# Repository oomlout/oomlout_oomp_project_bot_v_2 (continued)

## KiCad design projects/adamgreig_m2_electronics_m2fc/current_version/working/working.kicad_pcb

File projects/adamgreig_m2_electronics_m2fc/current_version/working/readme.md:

# m2_electronics
 
## summary 
* id: adamgreig_m2_electronics_m2fc
* user: adamgreig
* name: m2_electronics
* board: m2fc
* repo: https://github.com/adamgreig/m2-electronics
* src_file_repo_kicad_pcb: m2fc/pcb/m2fc.kicad_pcb
* src_file_repo_kicad_pcb_link: https://github.com/adamgreig/m2-electronics/tree/master/m2fc/pcb/m2fc.kicad_pcb

* src_file_repo_sch: 
* src_file_repo_sch_link: https://github.com/adamgreig/m2-electronics/tree/master/
* full details link: https://github.com/oomlout/oomlout_oomp_project_bot_v_2/tree/main/projects/adamgreig_m2_electronics_m2fc/current_version/working  

## schematic  
  
[schematic (pdf)](working_schematic.pdf) 

## pcb  

[board (pdf)](working.pdf)  

## working_bom
| Id | Designator | Footprint | Quantity | Designation | Supplier and ref |  | None | 
| --- | --- | --- | --- | --- | --- | --- | --- | 
| 1 | C101,C104,C106,C120,C124,C126,C119 | C0603 | 7 | 2Âµ2 |  |  | [''] | 
| 2 | C102,C103,C108,C110,C111,C112,C113,C115,C116,C209,C210,C211,C212,C222,C223,C224,C225,C235,C236,C237,C238,C301,C302,C307,C308,C310,C403,C404,C405,C406,C407,C408,C501,C502,C503,C601,C604,C612,C615,C623,C626,C114,C305,C304,C122 | C0603 | 45 | 100n |  |  | [''] | 
| 3 | C105,C125 | C0603 | 2 | 1n |  |  | [''] | 
| 4 | C107,C109,C204,C205,C206,C213,C217,C219,C226,C230,C231,C232,C239,C303,C309,C401,C402,C602,C605,C616,C624,C627,C218,C613,C306 | C0603 | 25 | 10Âµ |  |  | [''] | 
| 5 | C117,C608,C619,C630 | C0603 | 4 | 1Âµ |  |  | [''] | 
| 6 | C118,C201,C214,C227,C311,C609,C610,C620,C621,C631,C632 | C0603 | 11 | 10n |  |  | [''] | 
| 7 | C121,C123 | C0603 | 2 | 15p |  |  | [''] | 
| 8 | C202,C203,C215,C216,C228,C229 | C0603 | 6 | 82n |  |  | [''] | 
| 9 | C207,C208,C220,C221,C233,C234 | C0603 | 6 | 8.2n |  |  | [''] | 
| 10 | C312 | C0603 | 1 | 220n |  |  | [''] | 
| 11 | C313 | C0603 | 1 | 470n |  |  | [''] | 
| 12 | C314 | C0603 | 1 | 4Âµ7 |  |  | [''] | 
| 13 | C603,C606,C607,C611,C614,C617,C618,C622,C625,C628,C629,C633 | C1206 | 12 | 100n |  |  | [''] | 
| 14 | D101,D102,D201,D202,D203,D204,D205,D206,D406,D407,D504,D506,D603,D604,D605,D606,D601,D602,D502 | R0402 | 19 | CGA0402MLC-12G |  |  | [''] | 
| 15 | D402,D403,D404,D405 | LED0603 | 4 | YELLOW |  |  | [''] | 
| 16 | D501,D503,D505 | SOD323 | 3 | DIODESCH |  |  | [''] | 
| 17 | IC101,IC103 | MSOP8 | 2 | ADP3335 |  |  | [''] | 
| 18 | IC102 | LQFP100 | 1 | STM32F405VGT |  |  | [''] | 
| 19 | IC201,IC204,IC207 | MSOP8 | 3 | AD8226 |  |  | [''] | 
| 20 | IC202,IC208,IC602,IC604,IC606,IC205 | MSOP8 | 6 | AD8656 |  |  | [''] | 
| 21 | IC203,IC206,IC209 | SC-70-5 | 3 | AD8541 |  |  | [''] | 
| 22 | IC301 | ADXL3x5 | 1 | ADXL375 |  |  | [''] | 
| 23 | IC303 | MS5611-01BA | 1 | MS5611-01BA03 |  |  | [''] | 
| 24 | IC304 | HMC5883L | 1 | HMC5883L |  |  | [''] | 
| 25 | IC305 | L3G4200D | 1 | L3G4200D |  |  | [''] | 
| 26 | IC401 | SOIC16 | 1 | ADuM5201 |  |  | [''] | 
| 27 | IC402 | SOIC8 | 1 | ADuM1201 |  |  | [''] | 
| 28 | IC601,IC603,IC605 | MSOP8 | 3 | AD8495 |  |  | [''] | 
| 29 | P101,P402,P503,P601,P602,P603,P502,P501,P102,P103 | S02B-PASK-2 | 10 | CONN_2 |  |  | [''] | 
| 30 | P104 | FTSH-105-01-F-D-K | 1 | SWD |  |  | [''] | 
| 31 | P201,P202,P203,P403,P401 | S04B-PASK-2 | 5 | CONN_4 |  |  | [''] | 
| 32 | R101,R301,R304,R306,R307,R308,R501,R504,R506,R507,R508,R511,R513,R514,R515,R518,R520,R521,R303,R305,R302 | R0603 | 21 | 10k |  |  | [''] | 
| 33 | R102,R201,R209,R217,R601,R606,R608,R613,R615,R620 | R0603 | 10 | 1k |  |  | [''] | 
| 34 | R105,R106,R107,R104,R103 | R0603 | 5 | 47k |  |  | [''] | 
| 35 | R108,R401,R402,R403,R404,R405,R406,R407,R502,R503,R509,R510,R516,R517,R408 | R0603 | 15 | 100 |  |  | [''] | 
| 36 | R202,R208,R210,R218,R216,R224 | R0603 | 6 | 10k 0.05% |  |  | [''] | 
| 37 | R203,R211,R219 | R0603 | 3 | 330 |  |  | [''] | 
| 38 | R204,R212,R220 | R0603 | 3 | 1.69k |  |  | [''] | 
| 39 | R205,R213,R221 | R0603 | 3 | 6.04k |  |  | [''] | 
| 40 | R206,R214,R222 | R0603 | 3 | 562 |  |  | [''] | 
| 41 | R207,R215,R223 | R0603 | 3 | 17.8k |  |  | [''] | 
| 42 | R505,R512,R519 | PWR4318 | 3 | 5 |  |  | [''] | 
| 43 | R602,R609,R616 | R0603 | 3 | 8.87k |  |  | [''] | 
| 44 | R603,R610,R617 | R0603 | 3 | 31.6k |  |  | [''] | 
| 45 | R604,R611,R618 | R0603 | 3 | 2.94k |  |  | [''] | 
| 46 | R605,R612,R619 | R0603 | 3 | 95.3k |  |  | [''] | 
| 47 | R607,R621,R614 | R0603 | 3 | 1M |  |  | [''] | 
| 48 | TP101,TP102,TP103,TP104,TP105,TP106,TP107,TP108,TP109,TP110,TP201,TP202,TP203,TP301,TP304,TP305,TP306,TP308,TP309,TP310,TP312,TP313,TP314,TP315,TP316,TP317,TP318,TP319,TP320,TP321,TP401,TP402,TP403,TP404,TP501,TP502,TP503,TP504,TP505,TP506,TP507,TP508,TP509,TP602,TP603,TP604,TP605,TP606,TP111,TP113,TP114,TP601 | TESTPAD | 52 | TESTPAD |  |  | [''] | 
| 49 | U106 | MICROSD | 1 | MICROSD |  |  | [''] | 
| 50 | Q501,Q503,Q505 | SOT-23-MOSFET | 3 | MOSFET_P |  |  | [''] | 
| 51 | Q502,Q504,Q506 | SOT-23-MOSFET | 3 | MOSFET_N |  |  | [''] | 
| 52 | U108,U109,U110,U111,U112,U107 | M3_MOUNT | 6 | MOUNT |  |  | [''] | 
| 53 | X101 | XTAL50x32 | 1 | 8M |  |  | [''] | 
| 54 | D401,D408 | LED0603 | 2 | RED |  |  | [''] | 
| 55 | IC302 | ADXL3x5 | 1 | ADXL345 |  |  | [''] | 
| 56 | U114 | cusf_logo_small | 1 | LOGO |  |  | [''] | 
| 57 | U113 | cusf_logo_full | 1 | LOGO |  |  | [''] | 

## bom_schematic
| Ref | Qnty | Value | Cmp name | Footprint | Description | Vendor | DNP | 
| --- | --- | --- | --- | --- | --- | --- | --- | 
| C101, C104, C106, C119, C120, C124, C126 | 7 | 2Âµ2 | C-RESCUE-m2fc | m2fc:C0603 |  |  |  | 
| C102, C103, C108, C110, C111, C112, C113, C114, C115, C116, C122 | 11 | 100n | C-RESCUE-m2fc | m2fc:C0603 |  |  |  | 
| C105, C125 | 2 | 1n | C-RESCUE-m2fc | m2fc:C0603 |  |  |  | 
| C107, C109 | 2 | 10Âµ | C-RESCUE-m2fc | m2fc:C0603 |  |  |  | 
| C117 | 1 | 1Âµ | C-RESCUE-m2fc | m2fc:C0603 |  |  |  | 
| C118 | 1 | 10n | C-RESCUE-m2fc | m2fc:C0603 |  |  |  | 
| C121, C123 | 2 | 15p | C-RESCUE-m2fc | m2fc:C0603 |  |  |  | 
| D101, D102 | 2 | CGA0402MLC-12G | CGA0402MLC-12G | m2fc:R0402 |  |  |  | 
| GS101 | 1 | GS2 | GS2 | Connect:GS2 |  |  |  | 
| IC101, IC103 | 2 | ADP3335 | ADP3335 | m2fc:MSOP8 |  |  |  | 
| IC102 | 1 | STM32F405VGT | STM32F405VGT | m2fc:LQFP100 |  |  |  | 
| P101, P102, P103 | 3 | CONN_2 | CONN_2 | m2fc:S02B-PASK-2 |  |  |  | 
| P104 | 1 | SWD | SWD | m2fc:FTSH-105-01-F-D-K |  |  |  | 
| R101 | 1 | 10k | R-RESCUE-m2fc | m2fc:R0603 |  |  |  | 
| R102 | 1 | 1k | R-RESCUE-m2fc | m2fc:R0603 |  |  |  | 
| R103, R104, R105, R106, R107 | 5 | 47k | R-RESCUE-m2fc | m2fc:R0603 |  |  |  | 
| R108 | 1 | 100 | R-RESCUE-m2fc | m2fc:R0603 |  |  |  | 
| TP101, TP102, TP103, TP104, TP105, TP106, TP107, TP108, TP109, TP110, TP111, TP113, TP114 | 13 | TESTPAD | TESTPAD | m2fc:TESTPAD |  |  |  | 
| U101 | 1 | BAT BOX | PART |  |  |  |  | 
| U102 | 1 | ARM SW | PART |  |  |  |  | 
| U103, U104, U105 | 3 | HOUSING | PART |  |  |  |  | 
| U106 | 1 | MICROSD | MICROSD | m2fc:MICROSD |  |  |  | 
| U107, U108, U109, U110, U111, U112 | 6 | MOUNT | PART | m2fc:M3_MOUNT |  |  |  | 
| U113 | 1 | LOGO | PART | m2fc:cusf_logo_full |  |  |  | 
| U114 | 1 | LOGO | PART | m2fc:cusf_logo_small |  |  |  | 
| X101 | 1 | 8M | CRYSTAL | m2fc:XTAL50x32 |  |  |  |

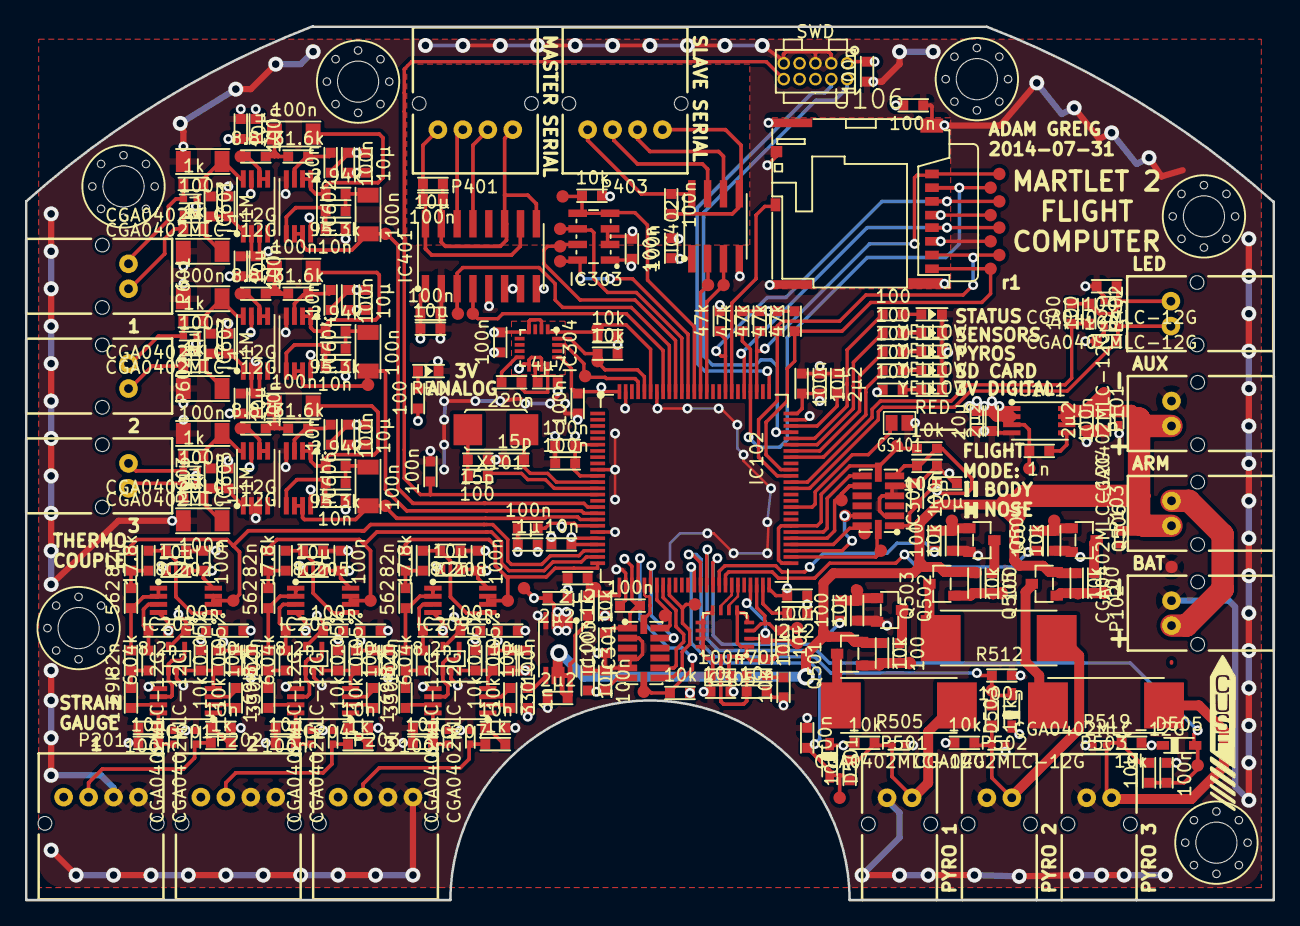
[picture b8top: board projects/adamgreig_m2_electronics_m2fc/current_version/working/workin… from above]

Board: 4 copper layers, 100.0 x 70.0 mm, 351 parts (1 on the bottom side), 170 nets.

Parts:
C101, C104, C106, C119, C120, C124, C126: 2µ2; C0603
C102, C103, C108, C110, C111, C112, C113, C114, C115, C116, C122, C209, C210, C211, C212, C222, C223, C224, C225, C235, C236, C237, C238, C301, C302, C304, C305, C307, C308, C310, C403, C404, C405, C406, C407, C408, C501, C502, C503, C601, C604, C612, C615, C623, C626: 100n; C0603
C105, C125: 1n; C0603
C107, C109, C204, C205, C206, C213, C217, C218, C219, C226, C230, C231, C232, C239, C303, C306, C309, C401, C402, C602, C605, C613, C616, C624, C627: 10µ; C0603
C117, C608, C619, C630: 1µ; C0603
C118, C201, C214, C227, C311, C609, C610, C620, C621, C631, C632: 10n; C0603
C121, C123: 15p; C0603
C202, C203, C215, C216, C228, C229: 82n; C0603
C207, C208, C220, C221, C233, C234: 8.2n; C0603
C312: 220n; C0603
C313: 470n; C0603
C314: 4µ7; C0603
C603, C606, C607, C611, C614, C617, C618, C622, C625, C628, C629, C633: 100n; C1206
D101, D102, D201, D202, D203, D204, D205, D206, D406, D407, D502, D504, D506, D601, D602, D603, D604, D605, D606: CGA0402MLC-12G; R0402
D401, D408: RED; LED0603
D402, D403, D404, D405: YELLOW; LED0603
D501, D503, D505: DIODESCH; SOD323
GS101: GS2
IC101, IC103: ADP3335; MSOP8
IC102: STM32F405VGT; LQFP100
IC201, IC204, IC207: AD8226; MSOP8
IC202, IC205, IC208, IC602, IC604, IC606: AD8656; MSOP8
IC203, IC206, IC209: AD8541; SC-70-5
IC301: ADXL375; ADXL3x5
IC302: ADXL345; ADXL3x5
IC303: MS5611-01BA03; MS5611-01BA
IC304: HMC5883L
IC305: L3G4200D
IC401: ADuM5201; SOIC16
IC402: ADuM1201; SOIC8
IC601, IC603, IC605: AD8495; MSOP8
P101, P102, P103, P402, P501, P502, P503, P601, P602, P603: CONN_2; S02B-PASK-2
P104: SWD; FTSH-105-01-F-D-K
P201, P202, P203, P401, P403: CONN_4; S04B-PASK-2
Q501, Q503, Q505: MOSFET_P; SOT-23-MOSFET
Q502, Q504, Q506: MOSFET_N; SOT-23-MOSFET
R101, R301, R302, R303, R304, R305, R306, R307, R308, R501, R504, R506, R507, R508, R511, R513, R514, R515, R518, R520, R521: 10k; R0603
R102, R201, R209, R217, R601, R606, R608, R613, R615, R620: 1k; R0603
R103, R104, R105, R106, R107: 47k; R0603
R108, R401, R402, R403, R404, R405, R406, R407, R408, R502, R503, R509, R510, R516, R517: 100; R0603
R202, R208, R210, R216, R218, R224: 10k 0.05%; R0603
R203, R211, R219: 330; R0603
R204, R212, R220: 1.69k; R0603
R205, R213, R221: 6.04k; R0603
R206, R214, R222: 562; R0603
R207, R215, R223: 17.8k; R0603
R505, R512, R519: 5; PWR4318
R602, R609, R616: 8.87k; R0603
R603, R610, R617: 31.6k; R0603
R604, R611, R618: 2.94k; R0603
R605, R612, R619: 95.3k; R0603
R607, R614, R621: 1M; R0603
TP101, TP102, TP103, TP104, TP105, TP106, TP107, TP108, TP109, TP110, TP111, TP113, TP114, TP201, TP202, TP203, TP301, TP304, TP305, TP306, TP308, TP309, TP310, TP312, TP313, TP314, TP315, TP316, TP317, TP318, TP319, TP320, TP321, TP401, TP402, TP403, TP404, TP501, TP502, TP503, TP504, TP505, TP506, TP507, TP508, TP509, TP601, TP602, TP603, TP604, TP605, TP606: TESTPAD
U106: MICROSD
U107, U108, U109, U110, U111, U112: MOUNT; M3_MOUNT
U113: LOGO; cusf_logo_full
U114: LOGO; cusf_logo_small
X101: 8M; XTAL50x32

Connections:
+3.3V: C103.1, C105.1, C106.1, C107.1, C108.1, C109.1, C110.1, C111.1, C112.1, C113.1, C114.1, C115.1, C116.1, C301.1, C302.1, C303.1, C304.1, C305.1, C306.1, C307.1, C308.1, C309.1, C310.1, C401.2, C403.2, C406.2, D501.2, D503.2, D505.2, IC101.1, IC101.2, IC101.3, IC102.6, IC102.11, IC102.19, IC102.28, IC102.50, IC102.75, IC102.100, IC301.1, IC301.6, IC302.1, IC302.6, IC303.1, IC304.2, IC304.4, IC304.13, IC305.1, IC305.4, IC305.5, IC305.15, IC305.16, IC401.1, IC401.6, IC401.7, IC402.1, P104.1, R103.1, R104.1, R105.1, R106.1, R107.1, R301.1, R302.1, R303.1, R304.1, R305.1, R306.1, R307.1, R401.2, R506.2, R513.2, R520.2, TP102.1, TP113.1, U106.4
+BATT: C102.1, C104.1, C124.1, D101.1, D102.1, IC101.6, IC101.7, IC101.8, IC103.6, IC103.7, IC103.8, P101.2, P103.2, Q501.S, Q503.S, Q505.S, R101.1, R501.2, R508.2, R515.2, TP104.1
/BAT_MON: C101.2, IC102.26, R101.2, R102.1, TP101.1
/IMU/BARO_CS: IC102.88, IC303.4, IC303.5, R307.2, TP321.1
/IMU/BARO_MISO: IC102.90, IC303.6, TP319.1
/IMU/BARO_MOSI: IC102.91, IC303.7, TP318.1
/IMU/BARO_SCK: IC102.89, IC303.8, TP317.1
/IMU/GYRO_DRDY: IC102.45, IC305.6
/IMU/GYRO_INT1: IC102.44, IC305.7
/IMU/GYRO_SCL: IC102.47, IC305.2, R305.2, TP313.1
/IMU/GYRO_SDA: IC102.48, IC305.3, R303.2, TP315.1
/IMU/HG_ACCEL_CS: IC102.29, IC301.7, R301.2, TP305.1
/IMU/HG_ACCEL_INT1: IC102.34, IC301.8, TP301.1
/IMU/HG_ACCEL_INT2: IC102.33, IC301.9
/IMU/HG_ACCEL_MISO: IC102.31, IC301.12
/IMU/HG_ACCEL_MOSI: IC102.32, IC301.13, TP309.1
/IMU/HG_ACCEL_SCK: IC102.30, IC301.14
/IMU/LG_ACCEL_CS: IC102.51, IC102.57, IC302.7, R302.2, TP306.1
/IMU/LG_ACCEL_INT1: IC102.56, IC302.8
/IMU/LG_ACCEL_INT2: IC102.55, IC302.9, TP304.1
/IMU/LG_ACCEL_MISO: IC102.53, IC302.12, TP308.1
/IMU/LG_ACCEL_MOSI: IC102.54, IC302.13, TP310.1
/IMU/LG_ACCEL_SCK: IC102.52, IC302.14, TP312.1
/IMU/MAGNO_DRDY: IC102.97, IC304.15, TP320.1
/IMU/MAGNO_SCL: IC102.95, IC304.1, R306.2, TP314.1
/IMU/MAGNO_SDA: IC102.96, IC304.16, R304.2, TP316.1
/IO/LED_1: IC102.68, R402.2
/IO/LED_2: IC102.69, R403.2
/IO/LED_3: IC102.70, R404.2
/IO/LED_4: IC102.71, R405.2
/IO/LED_A: IC102.64, R406.2, R407.2
/IO/LED_C: C407.1, D407.2, IC102.63, P402.2
/IO/SER_IN_1: IC102.93, IC401.4, TP402.1
/IO/SER_IN_2: IC102.87, IC402.2, TP403.1
/IO/SER_OUT_1: IC102.92, IC401.3, TP401.1
/IO/SER_OUT_2: IC102.86, IC402.3, TP404.1
/Pyros/PYRO_1_C: C501.1, D501.1, IC102.38, R507.2, TP503.1
/Pyros/PYRO_1_F: IC102.41, R502.2
/Pyros/PYRO_2_C: C502.1, D503.1, IC102.39, R514.2, TP506.1
/Pyros/PYRO_2_F: IC102.42, R509.2
/Pyros/PYRO_3_C: C503.1, D505.1, IC102.40, R521.2, TP509.1
/Pyros/PYRO_3_F: IC102.43, R516.2
/SD_CD: IC102.82, U106.11
/SD_CLK: IC102.80, TP110.1, U106.5
/SD_CMD: IC102.83, R107.2, TP109.1, U106.3
/SD_DAT0: IC102.65, R103.2, TP105.1, U106.7
/SD_DAT1: IC102.66, R104.2, TP106.1, U106.8
/SD_DAT2: IC102.78, R105.2, TP107.1, U106.1
/SD_DAT3: IC102.79, R106.2, TP108.1, U106.2
/SJ1: GS101.2, IC102.60
/SWCLK: IC102.76, P104.4
/SWDIO: IC102.72, P104.2
/StrainGauges/STRAIN_1: C203.1, IC102.23, IC202.6, IC202.7, TP201.1
/StrainGauges/STRAIN_2: C216.1, IC102.24, IC205.6, IC205.7, TP202.1
/StrainGauges/STRAIN_3: C229.1, IC102.25, IC208.6, IC208.7, TP203.1
/Thermocouples/THERMO_1: C607.1, IC102.16, IC602.6, IC602.7, TP602.1
/Thermocouples/THERMO_2: C618.1, IC102.17, IC604.6, IC604.7, TP604.1
/Thermocouples/THERMO_3: C629.1, IC102.18, IC606.6, IC606.7, TP606.1
/nRST: C122.2, IC102.14, P104.10
GND: C101.1, C102.2, C103.2, C104.2, C106.2, C107.2, C108.2, C109.2, C110.2, C111.2, C112.2, C113.2, C114.2, C115.2, C116.2, C117.2, C118.2, C119.2, C120.2, C121.2, C122.1, C123.2, C124.2, C126.2, C201.1, C204.2, C205.2, C206.2, C207.2, C208.2, C209.1, C210.1, C211.1, C212.2, C213.2, C214.1, C217.2, C218.2, C219.2, C220.2, C221.2, C222.1, C223.1, C224.1, C225.2, C226.2, C227.1, C230.2, C231.2, C232.2, C233.2, C234.2, C235.1, C236.1, C237.1, C238.2, C239.2, C301.2, C302.2, C303.2, C304.2, C305.2, C306.2, C307.2, C308.2, C309.2, C310.2, C311.1, C314.1, C401.1, C403.1, C405.1, C406.1, C407.2, C501.2, C502.2, C503.2, C601.2, C602.2, C603.1, C604.2, C605.2, C609.2, C610.2, C611.1, C612.2, C613.2, C614.1, C615.2, C616.2, C620.2, C621.2, C622.1, C623.2, C624.2, C625.1, C626.2, C627.2, C631.2, C632.2, C633.1, D101.2, D102.2, D201.1, D202.1, D203.1, D204.1, D205.1, D206.1, D401.2, D402.2, D403.2, D404.2, D405.2, D406.1, D407.1, D408.2, D502.2, D504.2, D506.2, D601.2, D602.2, D603.2, D604.2, D605.2, D606.2, GS101.1, IC101.4, IC102.10, IC102.20, IC102.27, IC102.74, IC102.94, IC102.99, IC103.4, IC201.5, IC202.4, IC203.2, IC204.5, IC205.4, IC206.2, IC207.5, IC208.4, IC209.2, IC301.2, IC301.4, IC301.5, IC302.2, IC302.4, IC302.5, IC303.2, IC303.3, IC304.9, IC304.11, IC305.8, IC305.9, IC305.10, IC305.11, IC305.12, IC305.13, IC401.2, IC401.5, IC401.8, IC402.4, IC601.2, IC601.3, IC602.4, IC603.2, IC603.3, IC604.4, IC605.2, IC605.3, IC606.4, P101.1, P102.1, P104.3, P104.5, P104.9, P201.1, P201.2, P202.1, P202.2, P203.1, P203.2, P501.2, P502.2, P503.2, Q502.S, Q504.S, Q506.S, R102.2, R208.2, R216.2, R224.2, R308.2, R504.2, R511.2, R518.2, R607.2, R614.2, R621.2, TP103.1, TP114.1, U106.6, U106.9, U106.10
unnamed: C105.2, IC101.5
unnamed: C119.1, IC102.49
unnamed: C120.1, IC102.73
unnamed: C121.1, IC102.12, X101.1
unnamed: C123.1, R108.1, X101.2
unnamed: C125.2, IC103.5
unnamed: C201.2, IC201.1, R201.1
unnamed: C202.1, IC202.1, IC202.2, R206.2
unnamed: C202.2, R204.1, R205.2
unnamed: C203.2, R206.1, R207.2
unnamed: C207.1, IC202.3, R205.1
unnamed: C208.1, IC202.5, R207.1
unnamed: C214.2, IC204.1, R209.1
unnamed: C215.1, IC205.1, IC205.2, R214.2
unnamed: C215.2, R212.1, R213.2
unnamed: C216.2, R214.1, R215.2
unnamed: C220.1, IC205.3, R213.1
unnamed: C221.1, IC205.5, R215.1
unnamed: C227.2, IC207.1, R217.1
unnamed: C228.1, IC208.1, IC208.2, R222.2
unnamed: C228.2, R220.1, R221.2
unnamed: C229.2, R222.1, R223.2
unnamed: C233.1, IC208.3, R221.1
unnamed: C234.1, IC208.5, R223.1
unnamed: C311.2, C313.2, IC305.14
unnamed: C312.1, IC304.8
unnamed: C312.2, IC304.12
unnamed: C313.1, R308.1
unnamed: C314.2, IC304.10
unnamed: C402.1, C404.1, IC401.10, IC401.16, P401.1
unnamed: C402.2, C404.2, IC401.9, IC401.11, IC401.15, P401.4
unnamed: C405.2, D406.2, P402.1, R406.1, R407.1
unnamed: C408.1, IC402.5, P403.4
unnamed: C408.2, IC402.8, P403.1
unnamed: C603.2, C608.1, IC601.8, R601.1
unnamed: C606.1, IC602.1, IC602.2, R604.2
unnamed: C606.2, R602.1, R603.2
unnamed: C607.2, R604.1, R605.2
unnamed: C608.2, C611.2, IC601.1, R606.1, R607.1
unnamed: C609.1, IC602.3, R603.1
unnamed: C610.1, IC602.5, R605.1
unnamed: C614.2, C619.1, IC603.8, R608.1
unnamed: C617.1, IC604.1, IC604.2, R611.2
unnamed: C617.2, R609.1, R610.2
unnamed: C618.2, R611.1, R612.2
unnamed: C619.2, C622.2, IC603.1, R613.1, R614.1
unnamed: C620.1, IC604.3, R610.1
unnamed: C621.1, IC604.5, R612.1
unnamed: C625.2, C630.1, IC605.8, R615.1
unnamed: C628.1, IC606.1, IC606.2, R618.2
unnamed: C628.2, R616.1, R617.2
unnamed: C629.2, R618.1, R619.2
unnamed: C630.2, C633.2, IC605.1, R620.1, R621.1
unnamed: C631.1, IC606.3, R617.1
unnamed: C632.1, IC606.5, R619.1
unnamed: D202.2, P201.3, R201.2
unnamed: D204.2, P202.3, R209.2
unnamed: D206.2, P203.3, R217.2
unnamed: D401.1, R401.1
unnamed: D402.1, R402.1
unnamed: D403.1, R403.1
unnamed: D404.1, R404.1
unnamed: D405.1, R405.1
unnamed: D408.1, R408.1
unnamed: D502.1, P501.1, R505.1, R506.1, R507.1
unnamed: D504.1, P502.1, R512.1, R513.1, R514.1
unnamed: D506.1, P503.1, R519.1, R520.1, R521.1
unnamed: D601.1, P601.2, R601.2
unnamed: D602.1, P601.1, R606.2
unnamed: D603.1, P602.2, R608.2
unnamed: D604.1, P602.1, R613.2
unnamed: D605.1, P603.2, R615.2
unnamed: D606.1, P603.1, R620.2
unnamed: IC102.13, R108.2
unnamed: IC201.2, R203.1
unnamed: IC201.3, R203.2
unnamed: IC201.4, IC203.3, R202.2, R208.1
unnamed: IC201.6, IC203.1, IC203.4
unnamed: IC201.7, R204.2
unnamed: IC204.2, R211.1
unnamed: IC204.3, R211.2
unnamed: IC204.4, IC206.3, R210.2, R216.1
unnamed: IC204.6, IC206.1, IC206.4
unnamed: IC204.7, R212.2
unnamed: IC207.2, R219.1
unnamed: IC207.3, R219.2
unnamed: IC207.4, IC209.3, R218.2, R224.1
unnamed: IC207.6, IC209.1, IC209.4
unnamed: IC207.7, R220.2
unnamed: IC401.13, P401.3
unnamed: IC401.14, P401.2
unnamed: IC402.6, P403.3
unnamed: IC402.7, P403.2
unnamed: IC601.5, IC601.6, R602.2, TP601.1
unnamed: IC603.5, IC603.6, R609.2, TP603.1
unnamed: IC605.5, IC605.6, R616.2, TP605.1
unnamed: P102.2, P103.1
unnamed: Q501.D, R505.2
unnamed: Q501.G, R501.1, R503.1, TP501.1
unnamed: Q502.D, R503.2
unnamed: Q502.G, R502.1, R504.1, TP502.1
unnamed: Q503.D, R512.2
unnamed: Q503.G, R508.1, R510.1, TP504.1
unnamed: Q504.D, R510.2
unnamed: Q504.G, R509.1, R511.1, TP505.1
unnamed: Q505.D, R519.2
unnamed: Q505.G, R515.1, R517.1, TP507.1
unnamed: Q506.D, R517.2
unnamed: Q506.G, R516.1, R518.1, TP508.1
VAA: C117.1, C118.1, C125.1, C126.1, C204.1, C205.1, C206.1, C209.2, C210.2, C211.2, C212.1, C213.1, C217.1, C218.1, C219.1, C222.2, C223.2, C224.2, C225.1, C226.1, C230.1, C231.1, C232.1, C235.2, C236.2, C237.2, C238.1, C239.1, C601.1, C602.1, C604.1, C605.1, C612.1, C613.1, C615.1, C616.1, C623.1, C624.1, C626.1, C627.1, D201.2, D203.2, D205.2, IC102.21, IC102.22, IC103.1, IC103.2, IC103.3, IC201.8, IC202.8, IC203.5, IC204.8, IC205.8, IC206.5, IC207.8, IC208.8, IC209.5, IC601.7, IC602.8, IC603.7, IC604.8, IC605.7, IC606.8, P201.4, P202.4, P203.4, R202.1, R210.1, R218.1, R408.2, TP111.1
